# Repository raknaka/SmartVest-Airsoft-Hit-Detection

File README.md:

# 🎯 SmartVest - Airsoft Hit Detection System  

**SmartVest** is a smart wearable system designed for airsoft games and tactical training scenarios.  
It provides **real-time hit detection** by sensing BB pellet or rubber projectile impacts through an array of pressure and vibration sensors.  
Inspired by video game mechanics, SmartVest delivers immersive and measurable training by mapping impact zones and giving instant feedback to the player or trainer.  

---

## 🧩 Project Mockup  

Here's a visual mockup of the SmartVest system design:  

---

## 💡 What Does It Do?  

SmartVest detects and classifies hits from projectiles (BBs or rubber bullets) on a player’s body using multiple force and vibration sensors embedded within a vest. It is especially designed to:  

- **Track and identify projectile impacts**  
- **Map hit locations across multiple zones**  
- **Differentiate real hits from fake or foreign object contacts**  
- **Deliver immediate feedback (visual/audio)**  
- **Log and transmit hit data to a central server or controller**  

---

## 🚀 Features  

- 🔹 **Multi-zone sensor detection** across the vest  
- 🔹 **Impact classification** (projectile vs. non-projectile)  
- 🔹 **Wireless communication options**:  
  - **ESP-NOW** → ultra-fast (1–2 ms latency) between vest & gun  
  - **Wi-Fi** → real-time logging to server/dashboard  
  - **LoRa (optional)** → long-range outdoor operations  
- 🔹 **Customizable & modular system** → supports different body sizes, teams, and modes  
- 🔹 **Game-style feedback** → LEDs, buzzer, vibration  
- 🔹 **Weapon lock system** → disables gun when player is “eliminated”  

---

## ⚙️ System Architecture  

- **Vest Module (ESP32)**  
  Processes sensor data, tracks health, and gives feedback via buzzer, LEDs, or vibration.  

- **Weapon Module (ESP32-C3 Mini + Servo)**  
  Automatic lock/unlock mechanism to prevent eliminated players from shooting.  

- **Monitoring Dashboard (Server/Raspberry Pi)**  
  Displays real-time player health, team stats, and hit locations.  

---

## 🧪 Testing & Results  

### Projectile & Airsoft Testing  
- Works best at **5–10 m**.  
- Piezo sensors generate up to **14V**, while ESP32 ADC max is **3.3V** (4095).  
- Tested with **SIG Sauer P226 MK25 GBB handgun** (~100 m/s muzzle velocity).  
- Reliable detection at 5 m distance.  

### Heatmap Analysis  
- A **grid test** (60×60 mm and 100×200 mm) was used to simulate projectile impacts on the vest pad.  
- **Heatmaps** were generated using Python visualization to show impact distribution:  
  - **Center areas** (closest to the sensor) produce the highest ADC readings.  
  - **Edges of the pad** show weaker signals, sometimes too low to be detected.  
  - Vibrations propagate to neighboring pads, but the **highest ADC value always corresponds to the direct hit pad**.  
- This proves SmartVest can **localize hits accurately** by identifying the strongest signal zone.  

*(Add images of heatmap here, e.g. 60x60 grid & 100x200 pad results)*  

### ESP-NOW Communication  
- Average latency: **1–2 ms**, with occasional spikes up to 45 ms due to interference.  
- Still fast and stable enough for **real-time weapon lock & feedback**.  

---

## 📂 Repository Contents  

- `firmware/` → ESP32 & ESP32-C3 source code  
- `hardware/` → PCB design files  
- `docs/` → diagrams, mockups, and test results  

---

## 📸 Prototype & Dashboard  

(Add your prototype photos, PCB screenshots, heatmap images, and monitoring UI here)  

---

## ⚡ Conclusion  

SmartVest integrates **real-time hit detection**, **automatic weapon lock**, and **centralized monitoring** into one system.  
Through **heatmap testing**, the system shows reliable hit localization and clear differentiation of impact zones.  
It enhances **fairness, sportmanship, and immersion** in airsoft games by combining IoT technology with game-like mechanics.  

---

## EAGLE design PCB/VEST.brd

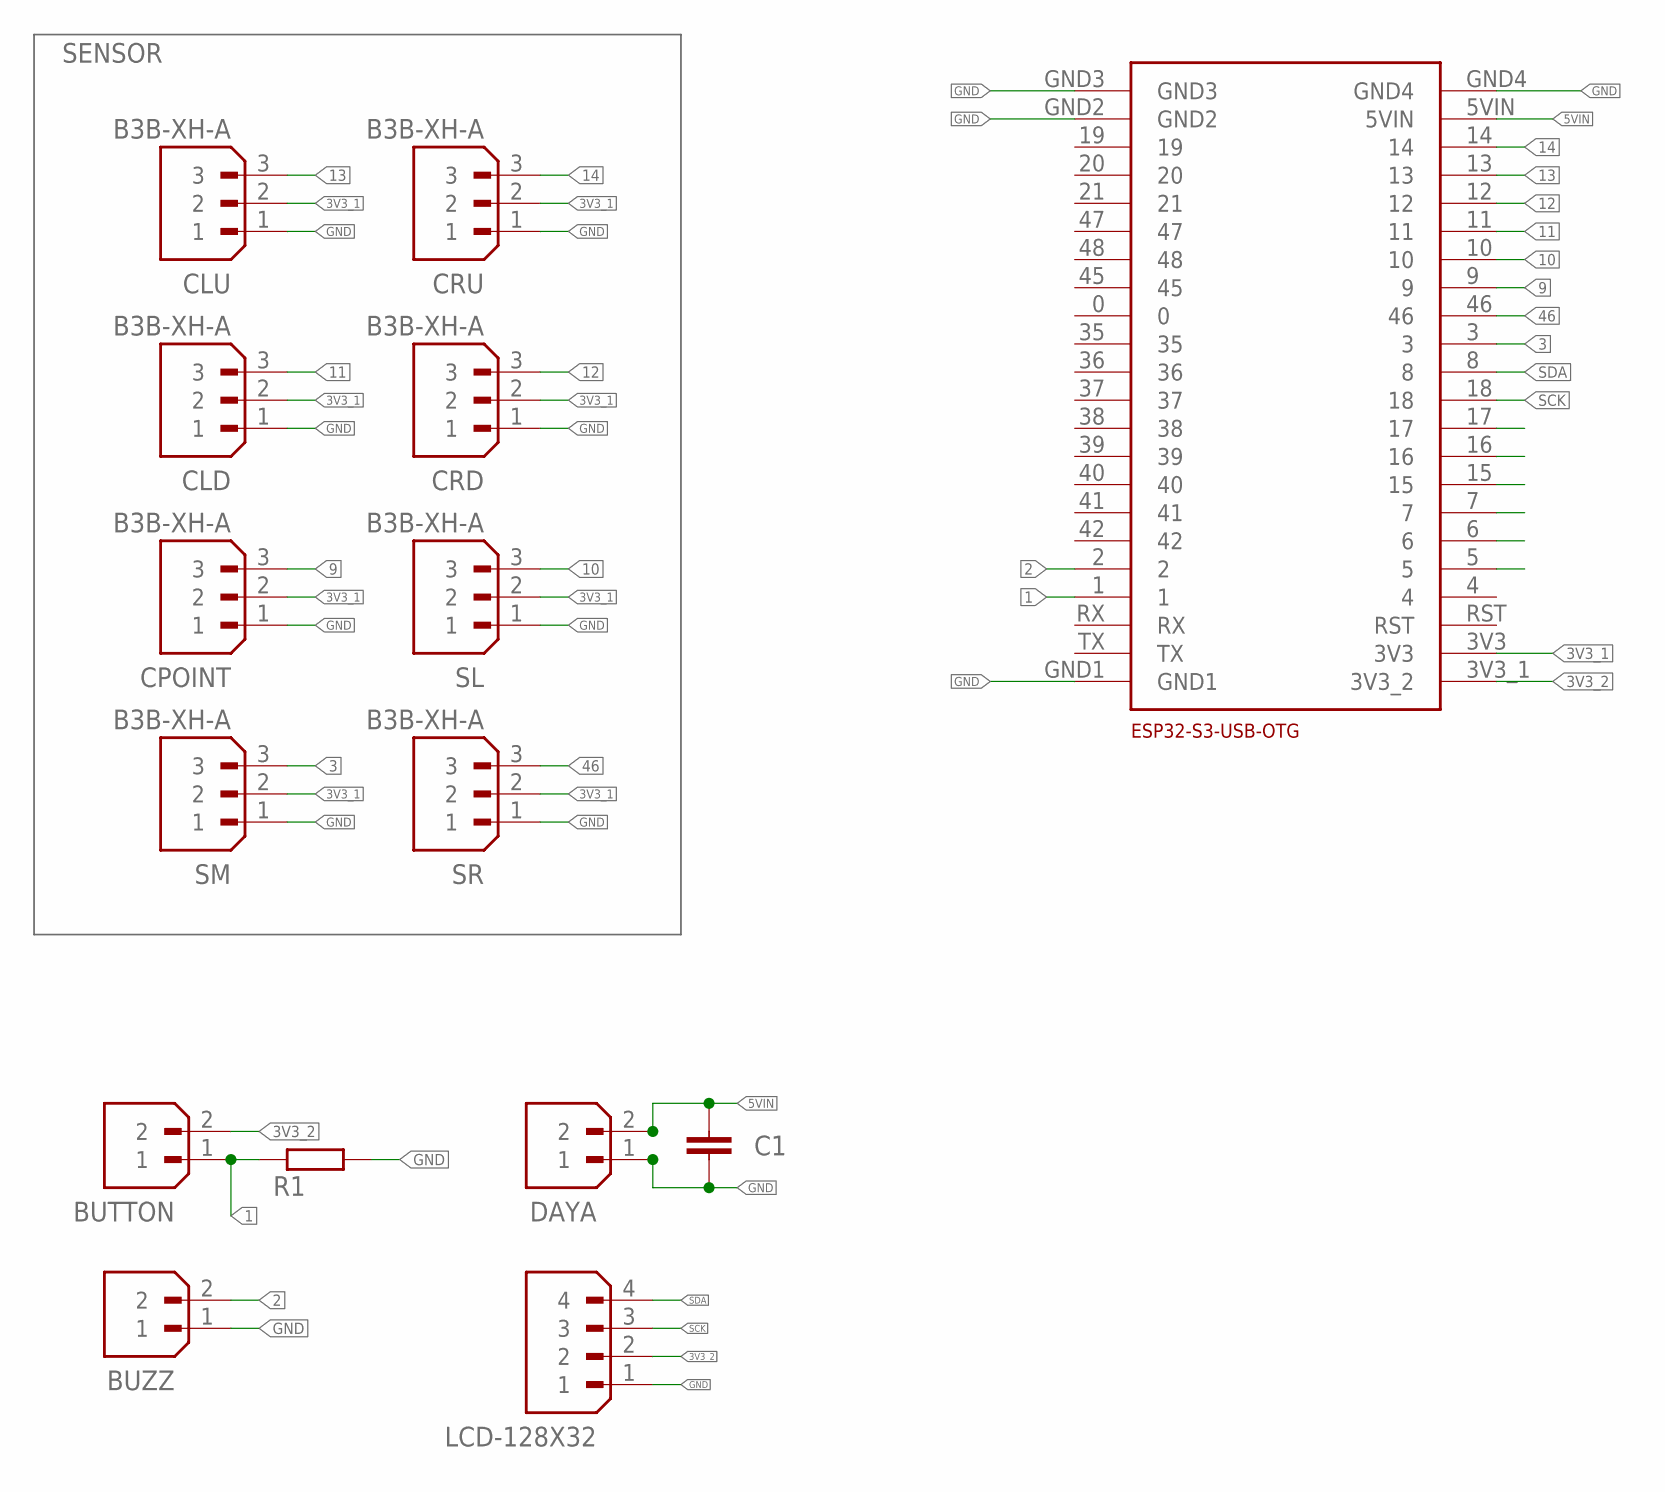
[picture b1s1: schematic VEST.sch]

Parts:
BUTTON: B2B-XH-A; JST_B2B-XH-A
BUZZ: B2B-XH-A; JST_B2B-XH-A
C1: C-EUC1206; C1206
CLD: B3B-XH-A; JST_B3B-XH-A
CLU: B3B-XH-A; JST_B3B-XH-A
CPOINT: B3B-XH-A; JST_B3B-XH-A
CRD: B3B-XH-A; JST_B3B-XH-A
CRU: B3B-XH-A; JST_B3B-XH-A
DAYA: B2B-XH-A; JST_B2B-XH-A
LCD-128X32: B4B-XH-A(LF)(SN); JST_B4B-XH-A(LF)(SN)
R1: R-EU_0207/10; 0207/10
SL: B3B-XH-A; JST_B3B-XH-A
SM: B3B-XH-A; JST_B3B-XH-A
SR: B3B-XH-A; JST_B3B-XH-A
U$1: ESP32-S3-DEVKIT; ESP32-S3-DEVKIT-USB-OTG

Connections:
1: BUTTON.1, R1.1, U$1.1
2: BUZZ.2, U$1.2
3: SM.3, U$1.3
3V3_1: CLD.2, CLU.2, CPOINT.2, CRD.2, CRU.2, SL.2, SM.2, SR.2, U$1.3V3
3V3_2: BUTTON.2, LCD-128X32.2, U$1.3V3_1 (3V3_2)
5VIN: C1.1, DAYA.2, U$1.5VIN
9: CPOINT.3, U$1.9
10: SL.3, U$1.10
11: CLD.3, U$1.11
12: CRD.3, U$1.12
13: CLU.3, U$1.13
14: CRU.3, U$1.14
46: SR.3, U$1.46
GND: BUZZ.1, C1.2, CLD.1, CLU.1, CPOINT.1, CRD.1, CRU.1, DAYA.1, LCD-128X32.1, R1.2, SL.1, SM.1, SR.1, U$1.GND1, U$1.GND2, U$1.GND3, U$1.GND4
SCK: LCD-128X32.3, U$1.18
SDA: LCD-128X32.4, U$1.8

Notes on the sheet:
SENSOR

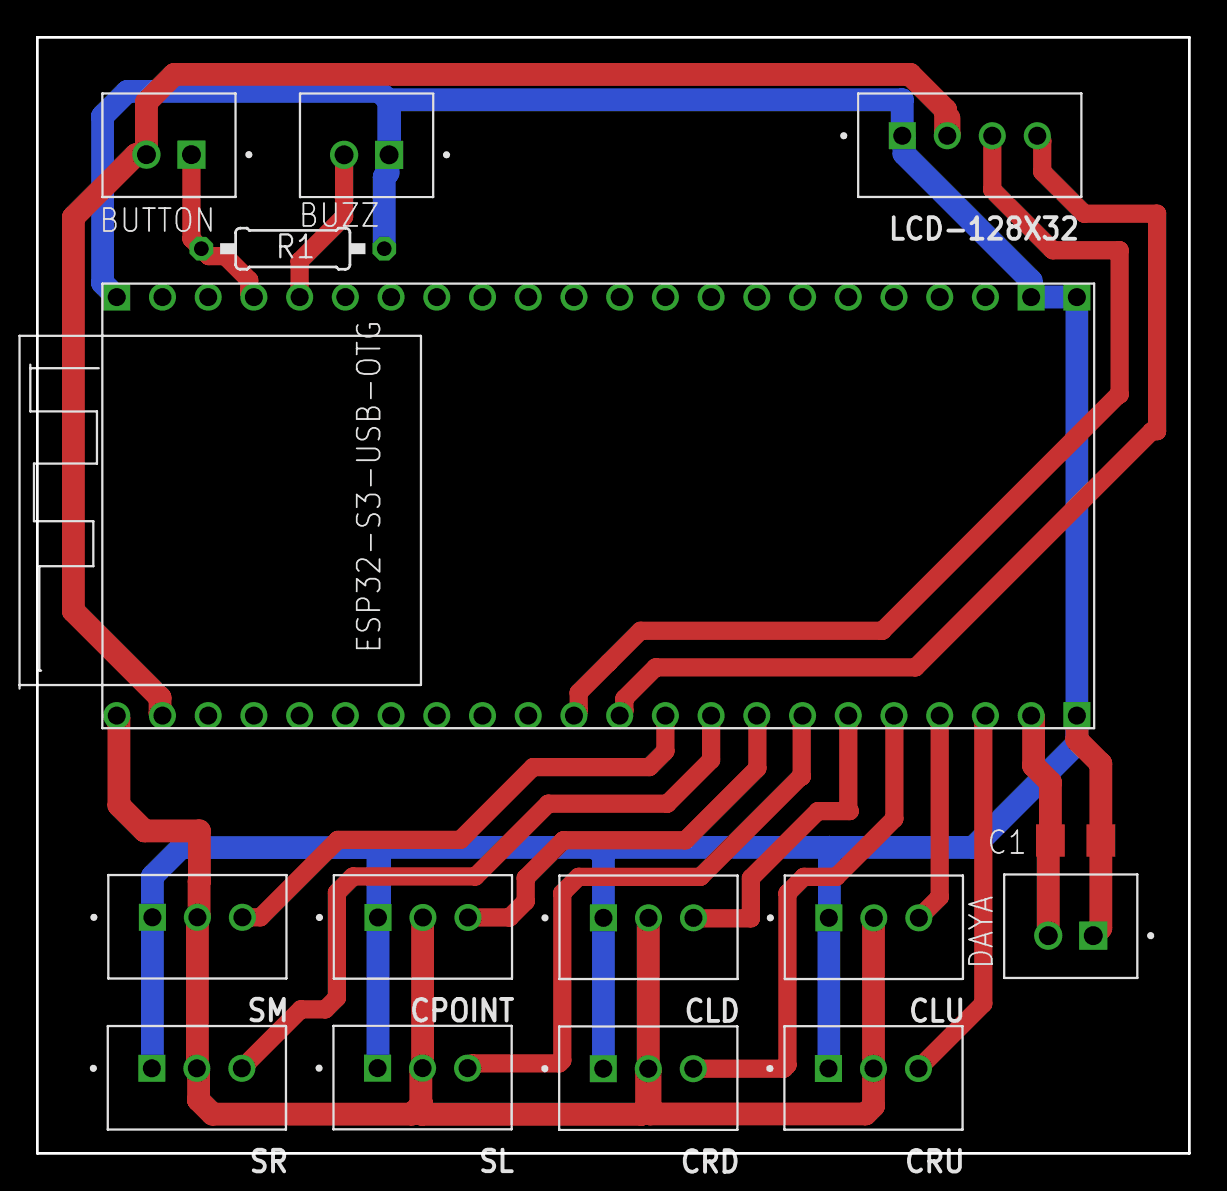
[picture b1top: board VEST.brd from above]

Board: 2 copper layers, 64.0 x 62.0 mm, 15 parts (0 on the bottom side), 16 nets.

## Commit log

2025-07-01 Update README.md
    Awal
2025-07-01 Update README.md
    Tambah gambar
2025-07-01 Update README.md
    Fix
    Gambar
2025-08-17 Add files via upload
    This is was the firmware for smartvest due to esp32 board
2025-08-17 Add files via upload
    This is was the pcb from the smartvest system this is just an input output from esp32 to all the component
2025-08-17 Update README.md
    An new information was added to this repo the content was the result from the prototipe
2025-08-17 Update README.md
    mantab
